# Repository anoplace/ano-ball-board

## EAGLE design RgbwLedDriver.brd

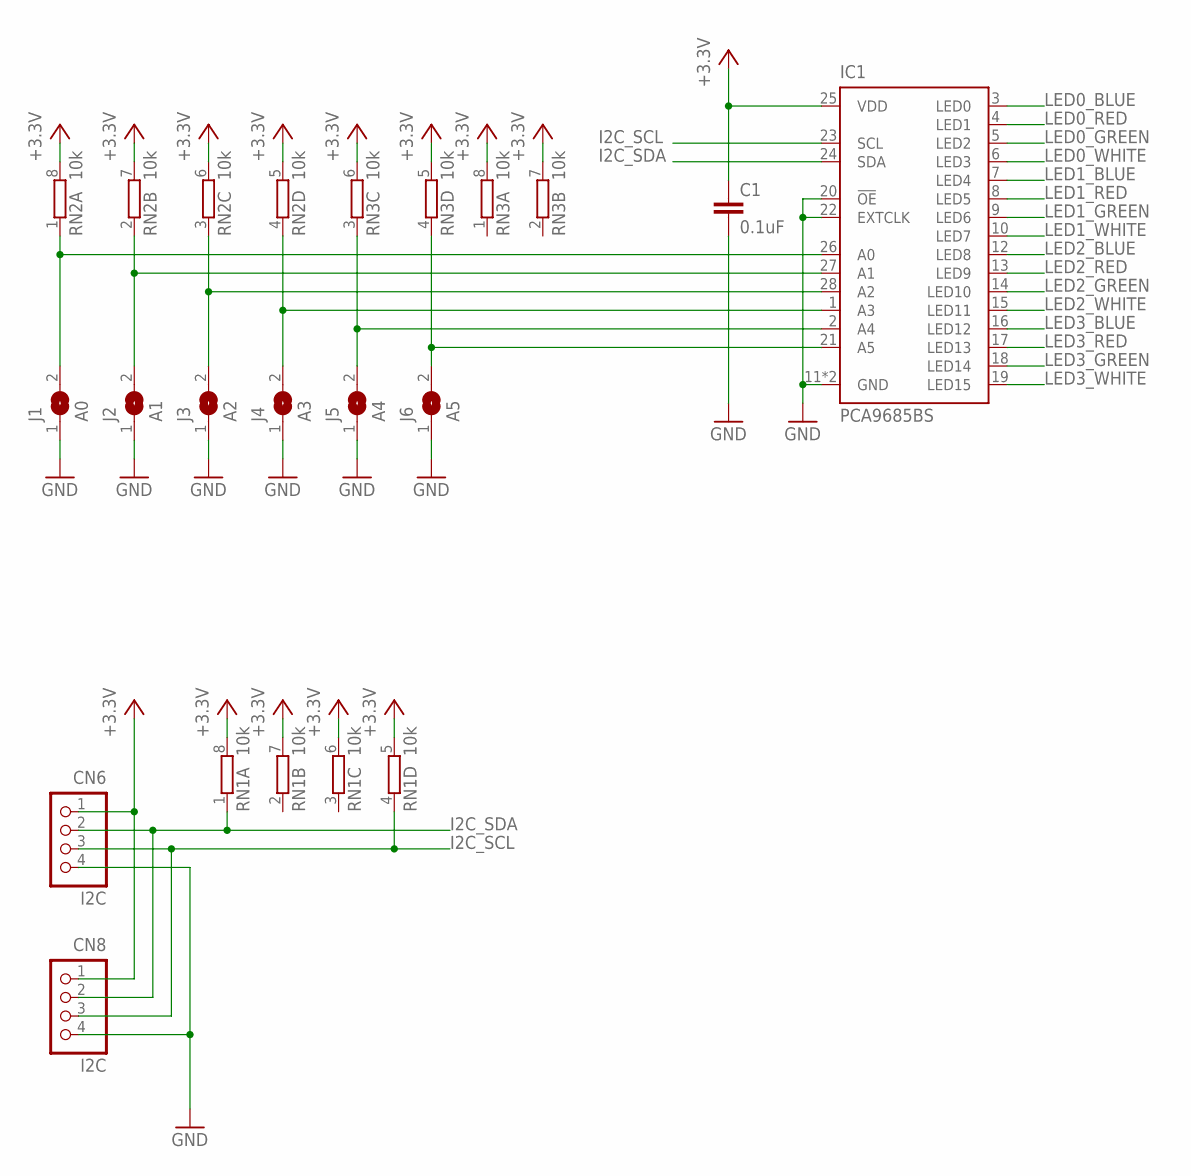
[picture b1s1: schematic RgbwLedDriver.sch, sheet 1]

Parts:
C1: 0.1uF; C0402
CN6, CN8: I2C; S4B-PH-K-S
IC1: PCA9685BS; QFN28-ML_6X6MM
J1: A0; SJ
J2: A1; SJ
J3: A2; SJ
J4: A3; SJ
J5: A4; SJ
J6: A5; SJ
RN1, RN2, RN3: 10k; EXB38V

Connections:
+3.3V: C1.1, CN6.1, CN8.1, IC1.25 (VDD), RN1.5 (2), RN1.6 (2), RN1.7 (2), RN1.8 (2), RN2.5 (2), RN2.6 (2), RN2.7 (2), RN2.8 (2), RN3.5 (2), RN3.6 (2), RN3.7 (2), RN3.8 (2)
GND: C1.2, CN6.4, CN8.4, IC1.11 (GND), IC1.20 (!OE!), IC1.22 (EXTCLK), IC1.EXP (GND), J1.1, J2.1, J3.1, J4.1, J5.1, J6.1; also elsewhere on the board
I2C_SCL: CN6.3, CN8.3, IC1.23 (SCL), RN1.4 (1)
I2C_SDA: CN6.2, CN8.2, IC1.24 (SDA), RN1.1
LED0_BLUE: IC1.3 (LED0); also elsewhere on the board
LED0_GREEN: IC1.5 (LED2); also elsewhere on the board
LED0_RED: IC1.4 (LED1); also elsewhere on the board
LED0_WHITE: IC1.6 (LED3); also elsewhere on the board
LED1_BLUE: IC1.7 (LED4); also elsewhere on the board
LED1_GREEN: IC1.9 (LED6); also elsewhere on the board
LED1_RED: IC1.8 (LED5); also elsewhere on the board
LED1_WHITE: IC1.10 (LED7); also elsewhere on the board
LED2_BLUE: IC1.12 (LED8); also elsewhere on the board
LED2_GREEN: IC1.14 (LED10); also elsewhere on the board
LED2_RED: IC1.13 (LED9); also elsewhere on the board
LED2_WHITE: IC1.15 (LED11); also elsewhere on the board
LED3_BLUE: IC1.16 (LED12); also elsewhere on the board
LED3_GREEN: IC1.18 (LED14); also elsewhere on the board
LED3_RED: IC1.17 (LED13); also elsewhere on the board
LED3_WHITE: IC1.19 (LED15); also elsewhere on the board
unnamed: IC1.26 (A0), J1.2, RN2.1
unnamed: IC1.27 (A1), J2.2, RN2.2 (1)
unnamed: IC1.28 (A2), J3.2, RN2.3 (1)
unnamed: IC1.1 (A3), J4.2, RN2.4 (1)
unnamed: IC1.2 (A4), J5.2, RN3.3 (1)
unnamed: IC1.21 (A5), J6.2, RN3.4 (1)

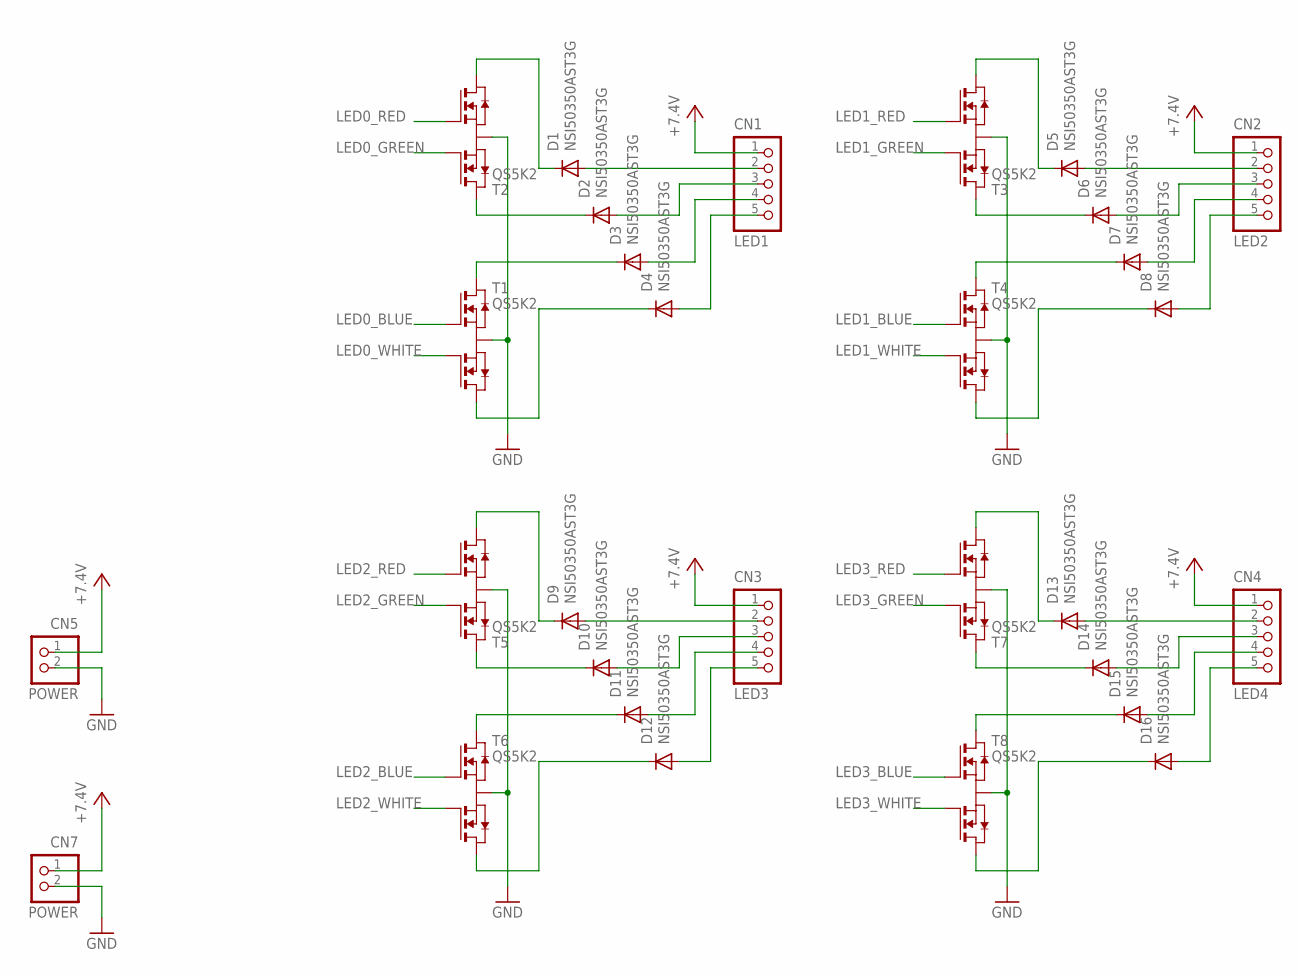
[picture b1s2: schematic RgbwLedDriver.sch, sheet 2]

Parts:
CN1: LED1; S5B-PH-K-S
CN2: LED2; S5B-PH-K-S
CN3: LED3; S5B-PH-K-S
CN4: LED4; S5B-PH-K-S
CN5, CN7: POWER; B2P-VH
D1, D2, D3, D4, D5, D6, D7, D8, D9, D10, D11, D12, D13, D14, D15, D16: NSI50350AST3G; SMC
T1, T2, T3, T4, T5, T6, T7, T8: QS5K2; SOT23-5L

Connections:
+7.4V: CN1.1, CN2.1, CN3.1, CN4.1, CN5.1, CN7.1
GND: CN5.2, CN7.2, T1.2 (S), T2.2 (S), T3.2 (S), T4.2 (S), T5.2 (S), T6.2 (S), T7.2 (S), T8.2 (S); also elsewhere on the board
LED0_BLUE: T1.1 (G1); also elsewhere on the board
LED0_GREEN: T2.1 (G1); also elsewhere on the board
LED0_RED: T2.3 (G2); also elsewhere on the board
LED0_WHITE: T1.3 (G2); also elsewhere on the board
LED1_BLUE: T4.1 (G1); also elsewhere on the board
LED1_GREEN: T3.1 (G1); also elsewhere on the board
LED1_RED: T3.3 (G2); also elsewhere on the board
LED1_WHITE: T4.3 (G2); also elsewhere on the board
LED2_BLUE: T6.1 (G1); also elsewhere on the board
LED2_GREEN: T5.1 (G1); also elsewhere on the board
LED2_RED: T5.3 (G2); also elsewhere on the board
LED2_WHITE: T6.3 (G2); also elsewhere on the board
LED3_BLUE: T8.1 (G1); also elsewhere on the board
LED3_GREEN: T7.1 (G1); also elsewhere on the board
LED3_RED: T7.3 (G2); also elsewhere on the board
LED3_WHITE: T8.3 (G2); also elsewhere on the board
unnamed: CN1.2, D1.A
unnamed: D2.C, T2.5 (D1)
unnamed: D6.C, T3.5 (D1)
unnamed: D1.C, T2.4 (D2)
unnamed: D4.C, T1.4 (D2)
unnamed: CN1.3, D2.A
unnamed: CN1.5, D4.A
unnamed: CN1.4, D3.A
unnamed: D3.C, T1.5 (D1)
unnamed: D5.C, T3.4 (D2)
unnamed: D8.C, T4.4 (D2)
unnamed: CN2.2, D5.A
unnamed: CN2.3, D6.A
unnamed: CN2.5, D8.A
unnamed: CN2.4, D7.A
unnamed: D7.C, T4.5 (D1)
unnamed: D10.C, T5.5 (D1)
unnamed: D9.C, T5.4 (D2)
unnamed: D12.C, T6.4 (D2)
unnamed: CN3.2, D9.A
unnamed: CN3.3, D10.A
unnamed: CN3.5, D12.A
unnamed: CN3.4, D11.A
unnamed: D11.C, T6.5 (D1)
unnamed: D14.C, T7.5 (D1)
unnamed: D13.C, T7.4 (D2)
unnamed: D16.C, T8.4 (D2)
unnamed: CN4.2, D13.A
unnamed: CN4.3, D14.A
unnamed: CN4.5, D16.A
unnamed: CN4.4, D15.A
unnamed: D15.C, T8.5 (D1)

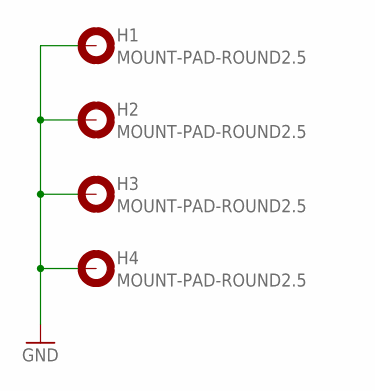
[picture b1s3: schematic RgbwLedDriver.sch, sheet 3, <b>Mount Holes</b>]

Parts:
H1, H2, H3, H4: MOUNT-PAD-ROUND2.5; 2,5-PAD

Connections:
GND: H1.B2,5, H2.B2,5, H3.B2,5, H4.B2,5; also elsewhere on the board

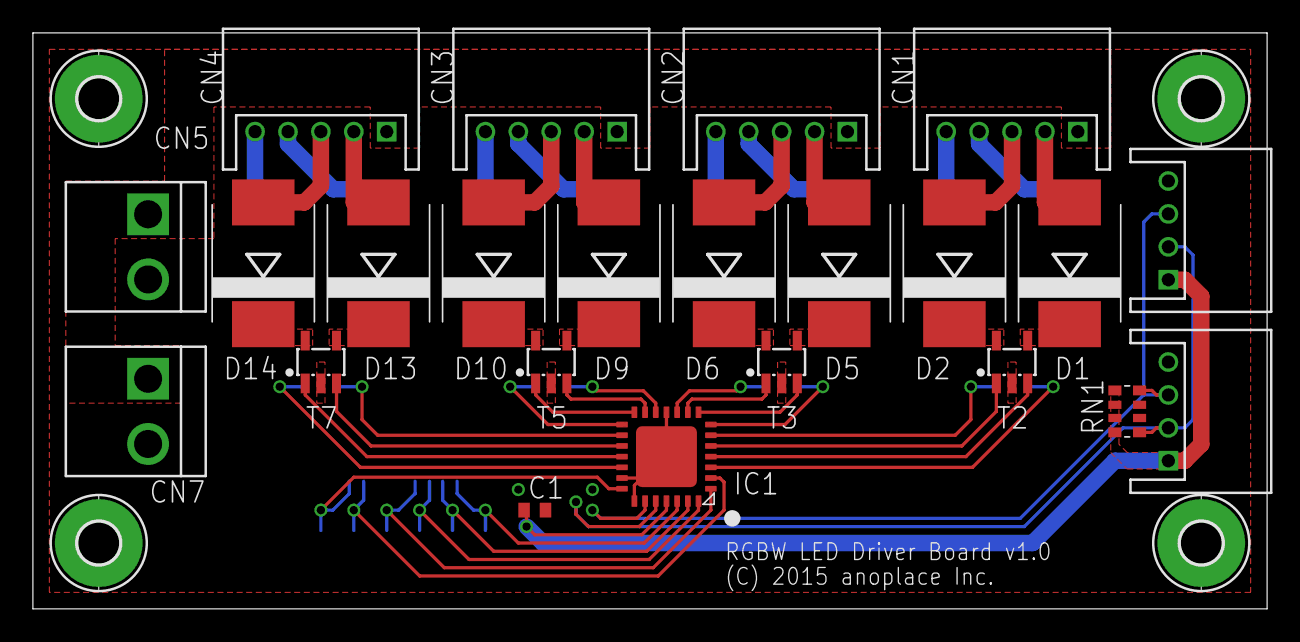
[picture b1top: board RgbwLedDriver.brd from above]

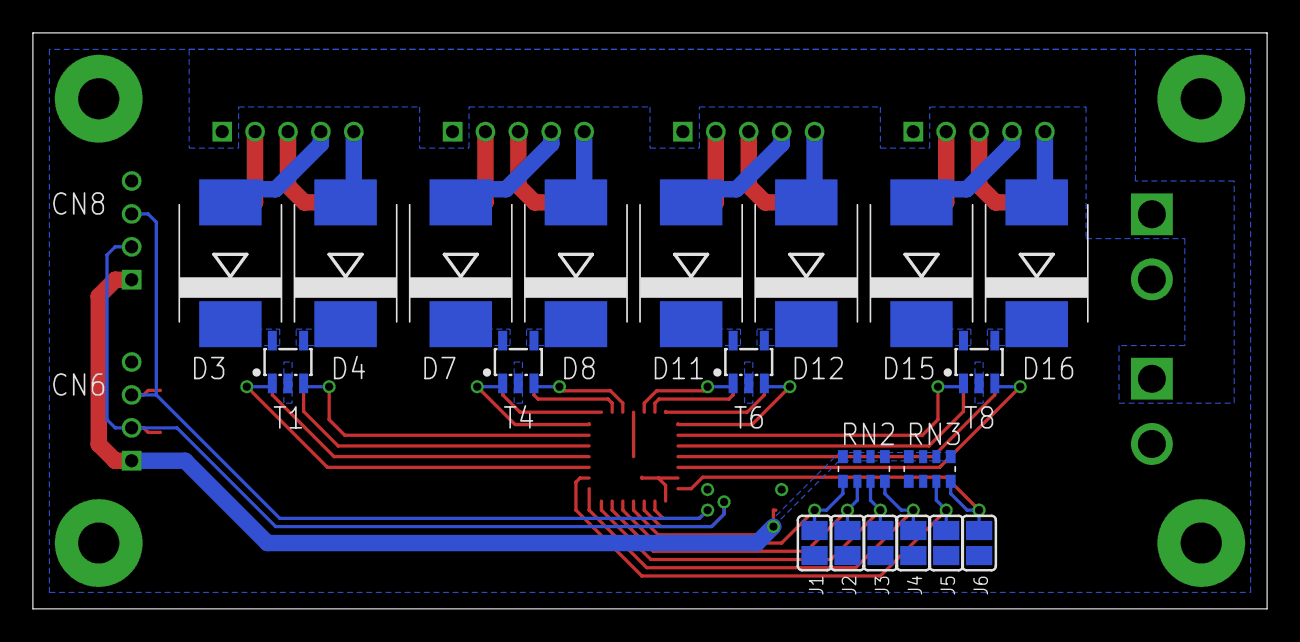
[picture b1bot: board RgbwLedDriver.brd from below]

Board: 4 copper layers, 75.0 x 35.0 mm, 47 parts (20 on the bottom side), 59 nets.

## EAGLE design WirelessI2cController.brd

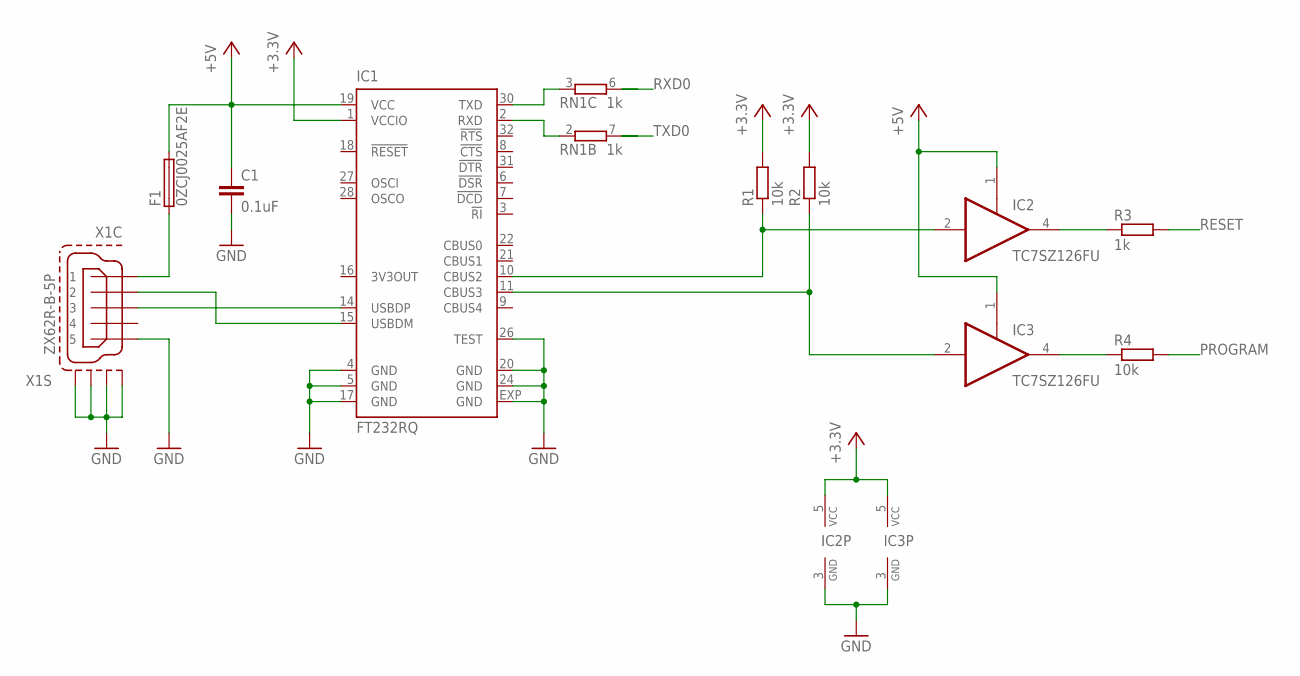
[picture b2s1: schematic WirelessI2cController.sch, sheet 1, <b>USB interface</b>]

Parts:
C1: 0.1uF; C0402
F1: 0ZCJ0025AF2E; 0ZCJ
IC1: FT232RQ; QFN32
IC2, IC3: TC7SZ126FU; SC70-5
R1, R2, R4: 10k; R0402
R3: 1k; R0402
RN1: 1k; EXB38V
X1: ZX62R-B-5P

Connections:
+3.3V: IC1.1 (VCCIO), IC2.5 (VCC), IC3.5 (VCC), R1.2, R2.2; also elsewhere on the board
+5V: C1.1, F1.2, IC1.19 (VCC), IC2.1 (OE), IC3.1 (OE)
GND: C1.2, IC1.4 (GND), IC1.5 (GND), IC1.17 (GND), IC1.20 (GND), IC1.24 (GND), IC1.26 (TEST), IC1.EXP (GND), IC2.3 (GND), IC3.3 (GND), X1.5, X1.S1, X1.S2, X1.S3, X1.S4; also elsewhere on the board
unnamed: IC1.14 (USBDP), X1.3
unnamed: IC1.15 (USBDM), X1.2
unnamed: F1.1, X1.1
unnamed: IC1.10 (CBUS2), IC2.2 (I), R1.1
unnamed: IC1.11 (CBUS3), IC3.2 (I), R2.1
unnamed: IC2.4 (O), R3.1
unnamed: IC3.4 (O), R4.1
unnamed: IC1.30 (TXD), RN1.3 (1)
unnamed: IC1.2 (RXD), RN1.2 (1)
PROGRAM: R4.2; also elsewhere on the board
RESET: R3.2; also elsewhere on the board
RXD0: RN1.6 (2); also elsewhere on the board
TXD0: RN1.7 (2); also elsewhere on the board

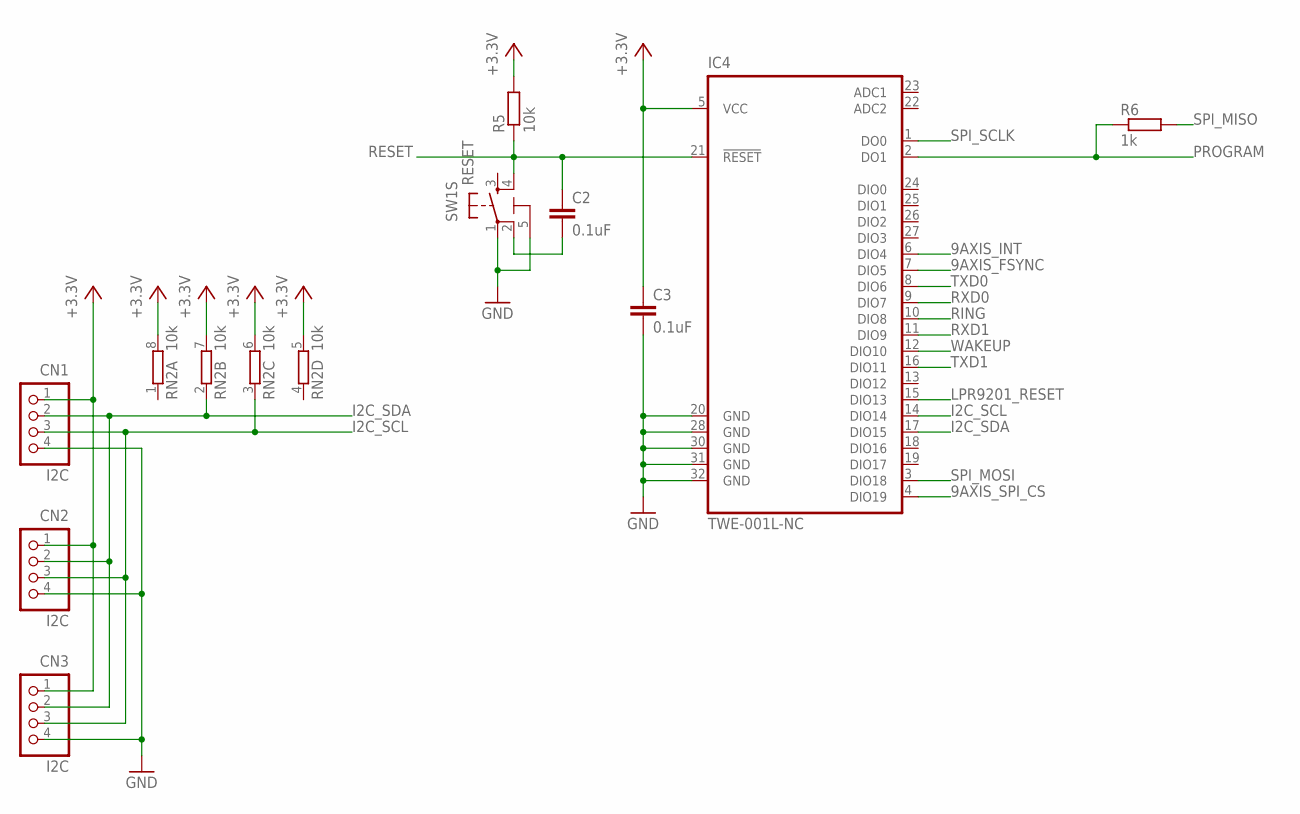
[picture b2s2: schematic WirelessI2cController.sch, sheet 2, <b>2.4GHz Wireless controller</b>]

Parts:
C2, C3: 0.1uF; C0402
CN1, CN2, CN3: I2C; B4B-PH-K-S
IC4: TWE-001L-NC; QFN32-HOLE
R5: 10k; R0402
R6: 1k; R0402
RN2: 10k; EXB38V
SW1: RESET; KMR2*G*

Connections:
9AXIS_FSYNC: IC4.7 (DIO5); also elsewhere on the board
9AXIS_INT: IC4.6 (DIO4); also elsewhere on the board
9AXIS_SPI_CS: IC4.4 (DIO19); also elsewhere on the board
+3.3V: C3.1, CN1.1, CN2.1, CN3.1, IC4.5 (VCC), R5.2, RN2.5 (2), RN2.6 (2), RN2.7 (2), RN2.8 (2); also elsewhere on the board
GND: C3.2, CN1.4, CN2.4, CN3.4, IC4.20 (GND), IC4.28 (GND), IC4.30 (GND), IC4.31 (GND), IC4.32 (GND), SW1.1, SW1.5; also elsewhere on the board
I2C_SCL: CN1.3, CN2.3, CN3.3, IC4.14 (DIO14), RN2.3 (1); also elsewhere on the board
I2C_SDA: CN1.2, CN2.2, CN3.2, IC4.17 (DIO15), RN2.2 (1); also elsewhere on the board
LPR9201_RESET: IC4.15 (DIO13); also elsewhere on the board
unnamed: C2.2, SW1.2 (P1)
PROGRAM: IC4.2 (DO1), R6.1; also elsewhere on the board
RESET: C2.1, IC4.21 (!RESET), R5.1, SW1.4 (S1); also elsewhere on the board
RING: IC4.10 (DIO8); also elsewhere on the board
RXD0: IC4.9 (DIO7); also elsewhere on the board
RXD1: IC4.11 (DIO9); also elsewhere on the board
SPI_MISO: R6.2; also elsewhere on the board
SPI_MOSI: IC4.3 (DIO18); also elsewhere on the board
SPI_SCLK: IC4.1 (DO0); also elsewhere on the board
TXD0: IC4.8 (DIO6); also elsewhere on the board
TXD1: IC4.16 (DIO11); also elsewhere on the board
WAKEUP: IC4.12 (DIO10); also elsewhere on the board

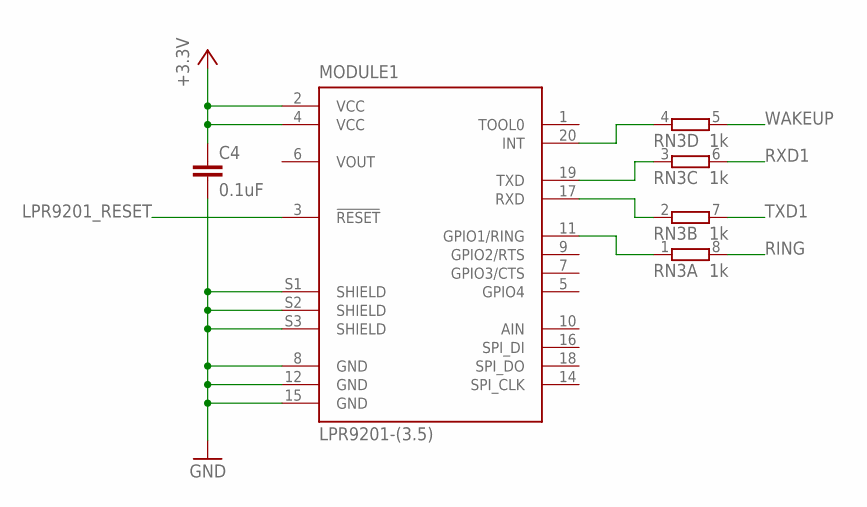
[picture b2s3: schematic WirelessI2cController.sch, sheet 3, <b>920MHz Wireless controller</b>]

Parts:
C4: 0.1uF; C0402
MODULE1: LPR9201-(3.5); DF12(*)-20DP-0.5V
RN3: 1k; EXB38V

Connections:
+3.3V: C4.1, MODULE1.2 (VCC), MODULE1.4 (VCC); also elsewhere on the board
GND: C4.2, MODULE1.8 (GND), MODULE1.12 (GND), MODULE1.15 (GND), MODULE1.S1 (SHIELD), MODULE1.S2 (SHIELD), MODULE1.S3 (SHIELD); also elsewhere on the board
LPR9201_RESET: MODULE1.3 (!RESET); also elsewhere on the board
unnamed: MODULE1.19 (TXD), RN3.3 (1)
unnamed: MODULE1.17 (RXD), RN3.2 (1)
unnamed: MODULE1.20 (INT), RN3.4 (1)
unnamed: MODULE1.11 (GPIO1/RING), RN3.1
RING: RN3.8 (2); also elsewhere on the board
RXD1: RN3.6 (2); also elsewhere on the board
TXD1: RN3.7 (2); also elsewhere on the board
WAKEUP: RN3.5 (2); also elsewhere on the board

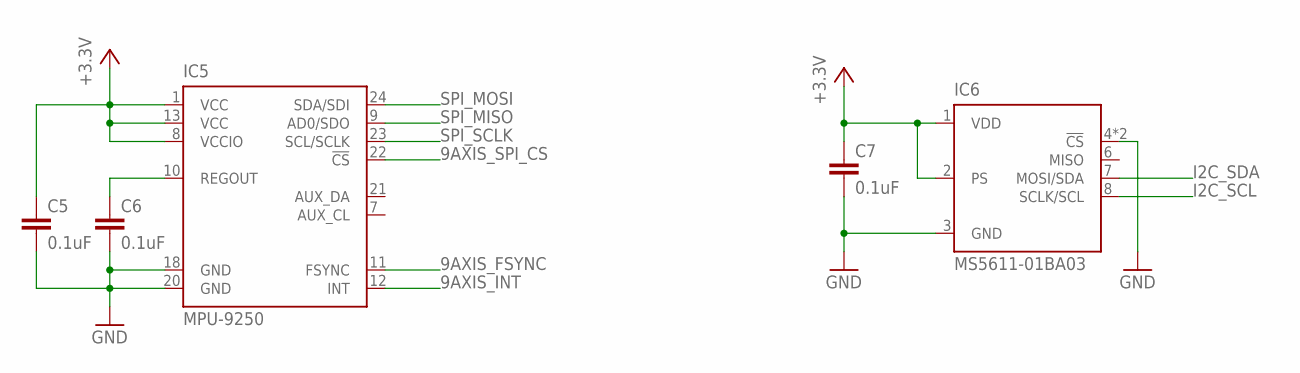
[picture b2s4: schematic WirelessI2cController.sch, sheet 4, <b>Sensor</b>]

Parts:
C5, C6, C7: 0.1uF; C0402
IC5: MPU-9250; QFN24-SMALL
IC6: MS5611-01BA03; LGA8

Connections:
9AXIS_FSYNC: IC5.11 (FSYNC); also elsewhere on the board
9AXIS_INT: IC5.12 (INT); also elsewhere on the board
9AXIS_SPI_CS: IC5.22 (!CS); also elsewhere on the board
+3.3V: C5.1, C7.1, IC5.1 (VCC), IC5.8 (VCCIO), IC5.13 (VCC), IC6.1 (VDD), IC6.2 (PS); also elsewhere on the board
GND: C5.2, C6.2, C7.2, IC5.18 (GND), IC5.20 (GND), IC6.3 (GND), IC6.4 (!CS!), IC6.5 (!CS!); also elsewhere on the board
I2C_SCL: IC6.8 (SCLK/SCL); also elsewhere on the board
I2C_SDA: IC6.7 (MOSI/SDA); also elsewhere on the board
unnamed: C6.1, IC5.10 (REGOUT)
SPI_MISO: IC5.9 (AD0/SDO); also elsewhere on the board
SPI_MOSI: IC5.24 (SDA/SDI); also elsewhere on the board
SPI_SCLK: IC5.23 (SCL/SCLK); also elsewhere on the board

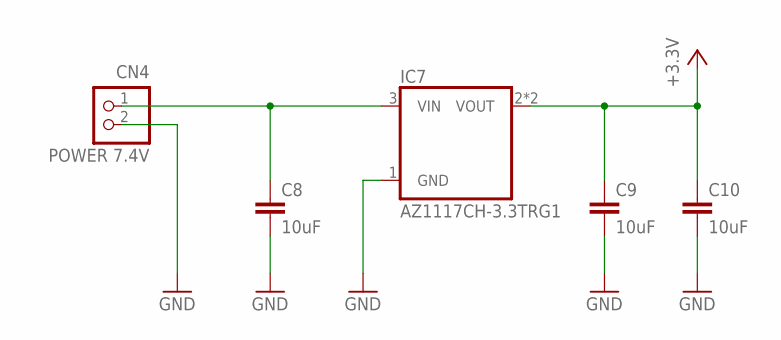
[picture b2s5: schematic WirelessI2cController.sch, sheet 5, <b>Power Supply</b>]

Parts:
C8, C9, C10: 10uF; C0805
CN4: POWER 7.4V; S2B-PH-K-S
IC7: AZ1117CH-3.3TRG1; SOT223

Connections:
+3.3V: C9.1, C10.1, IC7.2 (VOUT), IC7.4 (VOUT); also elsewhere on the board
GND: C8.2, C9.2, C10.2, CN4.2, IC7.1 (GND); also elsewhere on the board
unnamed: C8.1, CN4.1, IC7.3 (VIN)

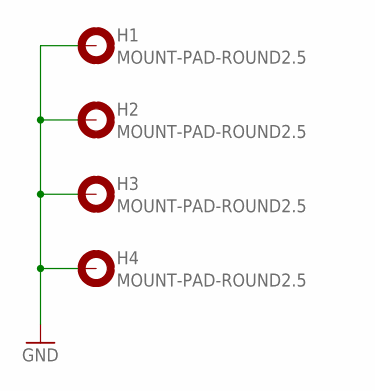
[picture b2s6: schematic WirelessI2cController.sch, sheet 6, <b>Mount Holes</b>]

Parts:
H1, H2, H3, H4: MOUNT-PAD-ROUND2.5; 2,5-PAD

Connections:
GND: H1.B2,5, H2.B2,5, H3.B2,5, H4.B2,5; also elsewhere on the board

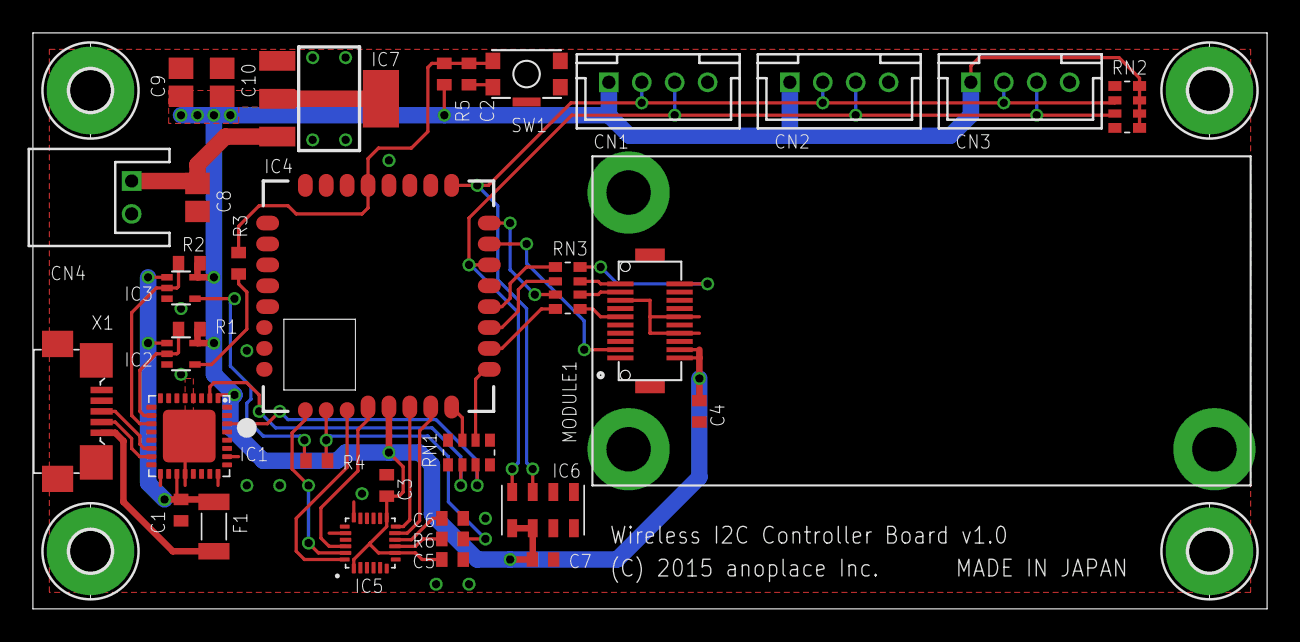
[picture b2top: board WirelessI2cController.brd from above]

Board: 4 copper layers, 75.0 x 35.0 mm, 38 parts (0 on the bottom side), 36 nets.

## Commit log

2015-03-28 プロジェクトを作成
2015-05-06 gitignoreを追加
2015-05-06 ライブラリをサブモジュールとして追加
2015-05-06 プロジェクトにライブラリを追加
2015-05-12 Wireless I2C Controllerを追加
2015-05-12 RGBW LEDドライバを追加
2015-05-25 配線名を変更
2015-06-05 電圧のシンボルを3.3Vに変更
2015-06-09 電源のシンボルを変更
2015-06-09 ライブラリを更新

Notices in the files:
RgbwLedDriver.brd:
(C) 2015 anoplace Inc.
